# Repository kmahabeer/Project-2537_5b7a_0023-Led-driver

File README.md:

# LED Driver Circuit

Welcome to my photogrammetry project! Within this repository, you will find the KiCad PCB design, as well as the firmware for the LED driver circuit. The LED driver circuit is a crucial component in my photogrammetry project.

## Introduction

My photogrammetry project focuses on creating photorealistic digital clones using a low-budget image capture system with precise illumination facilitated by several LED driver circuits. Precise, multispectral lighting is important for accurate image capture. The images captured are used to recreate texture maps, including diffuse, specular, and roughness maps. Additionally, the images captured serve as valuable training data for creating deepfake models.

The LED driver circuit consists of constant current drivers powering five LEDs, including RGB LEDs, a PC Amber LED, and a neutral white LED. Each circuit incorporates a cost-effective 8-bit Microchip PIC16 microcontroller. Ethernet communication between a main computer through a Power over Ethernet (PoE) switch will be used<sup><a href="#item1">[1]</a></sup>. The microcontroller will most likely implement a lightweight TCP/IP stack where a main computer sends either UDP or TCP packets. While a UDP or TCP packet can be sent via simple commands from the main computer, a custom application will be developed to automate this process once several LED driver circuits are implemented.

Please note that the resources herein are intended solely for this specific project and should not be used elsewhere. My intent for creating the photogrammetry project is my own personal use, and is not intended to create digital clones of anyone besides myself.

## Components

Some important components included in the schematic:

- Microchip PIC16F18026
- Microchip PD70210
- Cree LED JE2835 3V N-Class LEDs
- Luxeon 2835E Neutral White LEDs

## Directory Structure

- `LED-driver-kicad/`: KiCad schematic files (.sch), KiCad PCB layout files (.kicad_pcb) for the main circuit.
- `firmware/`: Any firmware-related code for the microcontroller.
- `Documentation/`: Any relevant documentation or datasheets used in the design.

## References

<ol>
<li id="item1">
“IEEE Standard for Information technology-- Local and metropolitan area networks-- Specific requirements-- Part 3: CSMA/CD Access Method and Physical Layer Specifications Amendment 3: Data Terminal Equipment (DTE) Power via the Media Dependent Interface (MDI) Enhancements” <i>IEEE Standards Association</i>, 30 Oct. 2009, <a href="https://standards.ieee.org/ieee/802.3at/4553/" target="_blank" rel="noopener noreferrer">standards.ieee.org/ieee/802.3at/4553/</a>.
</li>
</ol>

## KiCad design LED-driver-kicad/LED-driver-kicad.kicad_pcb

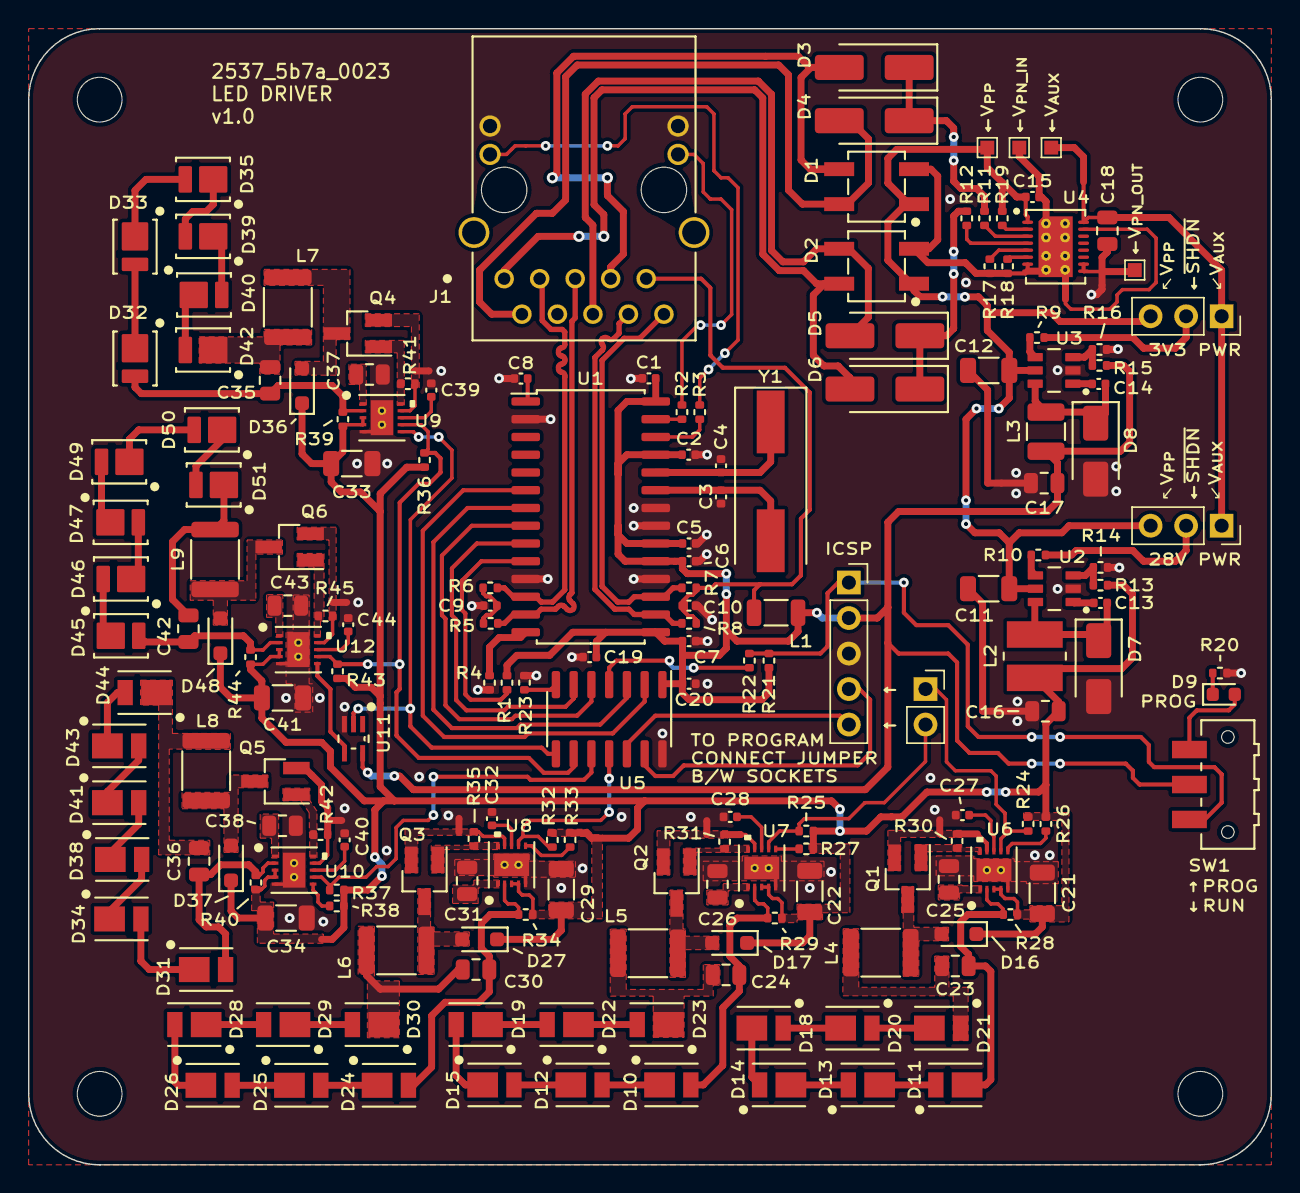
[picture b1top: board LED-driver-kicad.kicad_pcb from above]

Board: 2 copper layers, 88.9 x 81.3 mm, 192 parts (0 on the bottom side), 140 nets.

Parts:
C1, C2, C5, C6, C7, C9, C10, C13, C14, C15, C20: 100n; C_0402_1005Metric
C3, C4: 18p; C_0402_1005Metric
C8: 10u; C_0402_1005Metric
C11, C12: 2u2; C_1206_3216Metric
C16, C18, C23, C24, C25, C26, C30, C31, C35, C36, C37, C38, C42, C43: 4u7; C_0805_2012Metric
C17: 22u; C_0805_2012Metric
C19: 10n; C_0402_1005Metric
C21, C22, C29, C33, C34, C41: 10u; C_1206_3216Metric
C27, C28, C32, C39, C40, C44: 470p; C_0402_1005Metric
D1, D2: D_Bridge_+A-A; D_TO-269AA_4-BESOP_Diodes_MB10S-13
D3, D4, D5, D6: D; D_SMA_Handsoldering
D7, D8: SMC SS110; D_SMA
D9: GREEN; LED_0603_1608Metric
D10, D12, D15, D19, D22, D23: GREEN; LED_Cree-JE2835_3V_NClass_Group-1
D11, D13, D14, D18, D20, D21: RED; LED_Cree-JE2835_3V_NClass_Group-2
D16, D17, D27, D36, D37, D48: SD103AWS; D_SOD-323_HandSoldering
D24, D25, D26, D28, D29, D30: BLUE; LED_Cree-JE2835_3V_NClass_Group-1
D31, D34, D38, D41, D43, D44: PCAmber; LED_Cree-JE2835_3V_NClass_Group-1
D32, D33, D35, D39, D40, D42, D45, D46, D47, D49, D50, D51: White; LED_Lumiled_Luxeon_2835E_3V
H1, H2, H3, H4: MountingHole; MountingHole_3.2mm_M3
J1: ARJM11C7-114-BA-EW2; Connector_RJ45_Abracon_ARJM11C7-114-BA-EW2
J2, J3: Conn_01x03_Socket; PinSocket_1x03_P2.54mm_Vertical
J4: Conn_01x05_Socket; PinSocket_1x05_P2.54mm_Vertical
J5: Conn_01x02_Socket; PinSocket_1x02_P2.54mm_Vertical
L1: Ferrite Bead; L_1206_3216Metric
L2: 100u; L_TDK_VLS4015CX-6R8M-H
L3: 22u; L_1210_3225Metric
L4, L5, L6, L7, L8, L9: 330u; L_1812_4532Metric
NT1, NT2, NT3, NT4, NT5, NT6, NT7, NT8, NT9, NT10: NetTie_2; NetTie-2_SMD_Pad0.5mm
Q1, Q2, Q3, Q4, Q5, Q6: Q_NMOS_GDS; SOT-23_Handsoldering
R1, R11, R12, R14, R16, R21, R30, R31, R35, R41, R42, R45: 10k; R_0402_1005Metric
R2, R3: 1k; R_0402_1005Metric
R4: 2k32; R_0402_1005Metric
R5, R6, R7, R8: 49R9; R_0402_1005Metric
R9, R10, R24, R25, R26, R27, R32, R33, R36, R37, R38, R43: 100k; R_0402_1005Metric
R13: 357k; R_0402_1005Metric
R15: 33k; R_0402_1005Metric
R17: 60k4; R_0402_1005Metric
R18: 30R9; R_0402_1005Metric
R19: 25k; R_0402_1005Metric
R20: 100; R_0402_1005Metric
R22, R23: 470; R_0402_1005Metric
R28, R29, R34, R39, R40, R44: 1.43; R_0402_1005Metric
SW1: SW_SPDT; SW_SPDT_CK-JS102011SAQN
TP1, TP2, TP3, TP4: TestPoint; TestPoint_Pad_1.0x1.0mm
U1: ENC28J60x-SO; SOIC-28W_7.5x17.9mm_P1.27mm
U2, U3: LV2862XLVDDCR; SOT-23-Thin-6_DDC0006A-MFG_Regulator_Voltage_TI_LV2862XLVDD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
U4: PD70210A; DFN-16_5X4_MCH-Interface_PoE_Microchip_PD70210A
U5: PIC16F18026-ISL; SOIC-14_3.9x8.7mm_P1.27mm
U6, U7, U8, U9, U10, U12: MIC3205YML-TR; MLF-10_ML_MCH-Driver_LED_Microchip_MIC3205YML-TR
U11: 74AHC1G14; SOT-353-DCK5-Logic_Diodes_74AHC1G14SE-7
Y1: 25MHz; Crystal_SMD_HC49-SD

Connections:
+3.3V: C1.1, C2.1, C5.1, C6.1, C7.1, C17.1, C19.1, C20.1, J4.2, L1.1, L3.2, R1.2, R15.1, R21.1, SW1.2 (B), U1.15 (VDDTX), U1.19 (VDDRX), U1.20 (VDDPLL), U1.25 (VDDOSC), U1.28 (VDD), U5.1 (VDD), U11.5 (VCC)
+28V: C16.1, C21.1, C22.1, C29.1, C33.1, C34.1, C41.1, D16.1 (K), D17.1 (K), D27.1 (K), D36.1 (K), D37.1 (K), D48.1 (K), L2.2, R13.1, R24.1, R25.1, R26.1, R27.1, R28.1, R29.1, R32.1, R33.1, R34.1, R36.1, R37.1, R38.1, R39.1, R40.1, R43.1, R44.1, U6.3 (VIN), U6.4 (VINS), U7.3 (VIN), U7.4 (VINS), U8.3 (VIN), U8.4 (VINS), U9.3 (VIN), U9.4 (VINS), U10.3 (VIN), U10.4 (VINS), U12.3 (VIN), U12.4 (VINS)
/Ethernet/RJ45_LED_L_ANODE: J1.13 (LED), R2.2
/Ethernet/RJ45_LED_R_ANODE: J1.11 (LED), R3.2
/Ethernet/RJ45_RD+: J1.5 (RD+), R5.1, U1.13 (TPIN+)
/Ethernet/RJ45_RD-: J1.3 (RD-), R6.1, U1.12 (TPIN-)
/Ethernet/RJ45_TCT: C10.1, J1.9 (TCT), L1.2, R7.2, R8.1
/Ethernet/RJ45_TD+: J1.10 (TD+), R7.1, U1.17 (TPOUT+)
/Ethernet/RJ45_TD-: J1.8 (TD-), R8.2, U1.16 (TPOUT-)
/LEDs - amber and white/PGND_AMBER: NT8.2, Q5.3 (S), R42.2, U10.9 (PGND)
/LEDs - amber and white/PGND_WHITE: NT9.1, Q4.3 (S), R41.2, U9.9 (PGND)
/LEDs - amber and white/PGND_WHITE_P: NT10.1, Q6.3 (S), R45.2, U12.9 (PGND)
/LEDs/PGND_BLUE: NT7.2, Q3.3 (S), R35.2, U8.9 (PGND)
/LEDs/PGND_GREEN: NT5.2, Q2.3 (S), R31.2, U7.9 (PGND)
/LEDs/PGND_RED: NT6.2, Q1.3 (S), R30.2, U6.9 (PGND)
/Microcontroller/MCU_ICSP_MCLR: J4.1, R21.2, R22.1, SW1.1 (A)
/Power/3V3_C_{IN}_GND: C12.2, NT2.1
/Power/3V3_~SHDN: J2.2, R9.2
/Power/28V_C_{IN}_GND: C11.2, NT1.1
/Power/28V_~SHDN: J3.2, R10.2
/Power/VAUX: C18.1, J2.1, J3.1, TP3.1, U4.16 (VAUX)
/Power/VPN_IN: C15.2, D1.3 (-), D2.3 (-), NT3.1, R17.2, R18.2, TP2.1, U4.7 (VPN_IN), U4.8 (VPN_IN), U4.17 (ePAD)
/Power/VPN_OUT: C18.2, NT4.2, TP4.1, U4.9 (VPN_OUT), U4.10 (VPN_OUT)
/Power/VPP: C11.1, C12.1, C15.1, D1.1 (+), D2.1 (+), J2.3, J3.3, R19.1, TP1.1, U2.5 (VIN), U3.5 (VIN), U4.1 (VPP)
/Power/WA_EN: NT3.2, U4.15 (WA_EN)
GND: C1.2, C2.2, C3.1, C4.1, C5.2, C6.2, C7.2, C8.2, C9.2, C10.2, C16.2, C17.2, C19.2, C20.2, C21.2, C22.2, C25.2, C26.2, C27.2, C28.2, C29.2, C31.2, C32.2, C33.2, C34.2, C37.2, C38.2, C39.2, C40.2, C41.2, C43.2, C44.2, D7.2 (A), D8.2 (A), J1.12 (LED), J1.14 (LED), J4.3, NT1.2, NT2.2, NT4.1, NT5.1, NT6.1, NT7.1, NT8.1, NT9.2, NT10.2, R4.1, R14.2, R16.2, R20.1, R23.1, U1.2 (VSS), U1.11 (VSSRX), U1.18 (VSSTX), U1.21 (VSSPLL), U1.22 (VSSOSC), U2.2 (GND), U3.2 (GND), U5.14 (VSS), U6.5 (AGND), U6.11 (ePAD), U7.5 (AGND), U7.11 (ePAD), U8.5 (AGND), U8.11 (ePAD), U9.5 (AGND), U9.11 (ePAD), U10.5 (AGND), U10.11 (ePAD), U11.3 (GND), U12.5 (AGND), U12.11 (ePAD)
MCU_CCP1: R36.2, R43.2, U5.9 (RC1), U9.7 (DIM), U12.7 (DIM)
MCU_CCP2: R37.2, U5.10 (RC0), U10.7 (DIM)
MCU_PWM3_OUT: R32.2, U5.11 (RA2), U8.7 (DIM)
MCU_PWM4_OUT: J5.2, R25.2, U7.7 (DIM)
MCU_PWM5_OUT: J5.1, R24.2, U6.7 (DIM)
MCU_SPI_ETH_CS: U1.9 (~CS), U5.6 (RC4)
MCU_SPI_SCK: U1.8 (SCK), U5.5 (RC5)
MCU_SPI_SDI/MOSI: U1.6 (SO), U5.2 (RA5)
MCU_SPI_SDO/MISO: U1.7 (SI), U5.3 (RA4)
MCU_WHITE_LED: U5.8 (RC2), U9.6 (EN), U11.2
unnamed: C9.1, R5.2, R6.2
unnamed: D3.1 (K), D4.1 (K), R11.2
unnamed: D5.1 (K), D6.1 (K), R12.1
unnamed: C13.2, D7.1 (K), L2.1, U2.6 (SW)
unnamed: C14.2, D8.1 (K), L3.1, U3.6 (SW)
unnamed: D9.2 (A), SW1.3 (C)
unnamed: D9.1 (K), R20.2
unnamed: C24.1, D10.2 (A), R29.2, U7.2 (CS)
unnamed: D10.1 (K), D12.2 (A)
unnamed: C23.1, D11.2 (A), R28.2, U6.2 (CS)
unnamed: D11.1 (K), D13.2 (A)
unnamed: D12.1 (K), D15.2 (A)
unnamed: D13.1 (K), D14.2 (A)
unnamed: D14.1 (K), D18.2 (A)
unnamed: D15.1 (K), D19.2 (A)
unnamed: D16.2 (A), L4.2, Q1.2 (D)
unnamed: D17.2 (A), L5.2, Q2.2 (D)
unnamed: D18.1 (K), D20.2 (A)
unnamed: D19.1 (K), D22.2 (A)
unnamed: D20.1 (K), D21.2 (A)
unnamed: C23.2, D21.1 (K), L4.1
unnamed: D22.1 (K), D23.2 (A)
unnamed: C24.2, D23.1 (K), L5.1
unnamed: C30.1, D24.2 (A), R34.2, U8.2 (CS)
unnamed: D24.1 (K), D25.2 (A)
unnamed: D25.1 (K), D26.2 (A)
unnamed: D26.1 (K), D28.2 (A)
unnamed: D27.2 (A), L6.2, Q3.2 (D)
unnamed: D28.1 (K), D29.2 (A)
unnamed: D29.1 (K), D30.2 (A)
unnamed: C30.2, D30.1 (K), L6.1
unnamed: C36.1, D31.2 (A), R40.2, U10.2 (CS)
unnamed: D31.1 (K), D34.2 (A)
unnamed: C35.1, D32.2 (A), R39.2, U9.2 (CS)
unnamed: D32.1 (K), D33.2 (A)
unnamed: D33.1 (K), D35.2 (A)
unnamed: D34.1 (K), D38.2 (A)
unnamed: D35.1 (K), D39.2 (A)
unnamed: D36.2 (A), L7.2, Q4.2 (D)
unnamed: D37.2 (A), L8.2, Q5.2 (D)
unnamed: D38.1 (K), D41.2 (A)
unnamed: D39.1 (K), D40.2 (A)
unnamed: D40.1 (K), D42.2 (A)
unnamed: D41.1 (K), D43.2 (A)
unnamed: C35.2, D42.1 (K), L7.1
unnamed: D43.1 (K), D44.2 (A)
unnamed: C36.2, D44.1 (K), L8.1
unnamed: C42.1, D45.2 (A), R44.2, U12.2 (CS)
unnamed: D45.1 (K), D46.2 (A)
unnamed: D46.1 (K), D47.2 (A)
unnamed: D47.1 (K), D49.2 (A)
unnamed: D48.2 (A), L9.2, Q6.2 (D)
unnamed: D49.1 (K), D50.2 (A)
unnamed: D50.1 (K), D51.2 (A)
unnamed: C42.2, D51.1 (K), L9.1
unnamed: J4.4, U5.13 (RA0/ICSPDAT)
unnamed: J4.5, U5.12 (RA1/ICSPCLK)
unnamed: Q1.1 (G), R30.1, U6.10 (DRV)
unnamed: Q2.1 (G), R31.1, U7.10 (DRV)
unnamed: Q3.1 (G), R35.1, U8.10 (DRV)
unnamed: Q4.1 (G), R41.1, U9.10 (DRV)
unnamed: Q5.1 (G), R42.1, U10.10 (DRV)
unnamed: Q6.1 (G), R45.1, U12.10 (DRV)
unnamed: R2.1, U1.27 (LEDA)
unnamed: R3.1, U1.26 (LEDB)
unnamed: C3.2, U1.23 (OSC1), Y1.2
unnamed: C4.2, U1.24 (OSC2), Y1.1
unnamed: R4.2, U1.14 (RBIAS)
unnamed: C8.1, U1.1 (VCAP)
unnamed: R1.1, U1.10 (~RESET)
unnamed: C13.1, U2.1 (CB)
unnamed: R13.2, R14.1, U2.3 (FB)
unnamed: R10.1, U2.4 (~SHDN)
unnamed: C14.1, U3.1 (CB)
unnamed: R15.2, R16.1, U3.3 (FB)
unnamed: R9.1, U3.4 (~SHDN)
unnamed: R18.1, U4.6 (RCLS)
unnamed: R19.2, U4.2 (RDET)
unnamed: R17.1, U4.5 (RREF)
unnamed: R11.1, U4.3 (SUPP_S1)
unnamed: R12.2, U4.4 (SUPP_S2)
unnamed: R23.2, U5.7 (RC3)
unnamed: R22.2, U5.4 (~MCLR/Vpp/RA3)
unnamed: C27.1, U6.8 (CTIMER)
unnamed: R26.2, U6.6 (EN)
unnamed: C25.1, U6.1 (VCC)
unnamed: C28.1, U7.8 (CTIMER)
unnamed: R27.2, U7.6 (EN)
unnamed: C26.1, U7.1 (VCC)
unnamed: C32.1, U8.8 (CTIMER)
unnamed: R33.2, U8.6 (EN)
unnamed: C31.1, U8.1 (VCC)
unnamed: C39.1, U9.8 (CTIMER)
unnamed: C37.1, U9.1 (VCC)
unnamed: C40.1, U10.8 (CTIMER)
unnamed: R38.2, U10.6 (EN)
unnamed: C38.1, U10.1 (VCC)
unnamed: C44.1, U12.8 (CTIMER)
unnamed: U11.4, U12.6 (EN)
unnamed: C43.1, U12.1 (VCC)
RJ45_VC1+: D1.4, D3.2 (A), J1.7 (VC1+)
RJ45_VC1-: D1.2, D4.2 (A), J1.2 (VC1-)
RJ45_VC2+: D2.4, D5.2 (A), J1.6 (VC2+)
RJ45_VC2-: D2.2, D6.2 (A), J1.1 (VC2-)

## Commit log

2023-07-19 docs: create README.md
2023-07-19 create kicad project
2023-07-22 add gitignore
2023-07-22 docs: update README.md
2023-07-22 add symbols and footprints
2023-07-22 update KiCad schematic
2023-07-27 chore: add kicad library as submodule
2023-07-27 chore: add RJ45 connector and PoE controller symbols to kicad project library
2023-07-27 add separate hierarchical sheets for ethernet and main microcontroller
2023-07-27 chore: update kicad library submodule
2023-07-27 chore: update ethernet.kicad_sch
2023-07-27 chore: update Microcontroller.kicad_sch
2023-07-27 update symbol library locations
2023-07-27 update Memory_Microchip_25AA02E64T-IOT import
2023-07-27 update ENC28J60x-SO circuit
2023-07-27 update main schematic sheet and microcontroller
2023-07-27 remove unused libraries
2023-07-30 update library submodule and imports
2023-07-30 update schematic for RJ45 connector and Ethernet controller
2023-07-30 update schematic for main microcontroller
2023-07-30 add schematics for power controller and LEDs
2023-07-30 update main schematic sheet
2023-08-01 update Power schematic
2023-08-01 remove surge protection and wall adapter circuit
2023-08-01 update RGB LED driver circuits
2023-08-02 update *MCLR switch for microcontroller
2023-08-02 remove EEPROM MAC address IC
2023-08-02 remove VDDA decoupling
2023-08-02 add schematic sheet for white and PC amber LED
2023-08-02 update RGB LEDs
2023-08-02 connect unused IO to pull down resistor
2023-08-02 replace MOSFETs with generic n-channel MSOFETs
2023-08-02 replace push-pull MOSFET circuit with LED driver with inverter gate enable
2023-08-02 update comments and title blocks
2023-08-02 update 3V3 power supply circuit
2023-08-02 update 28V power supply circuit
2023-08-02 update component designators
2023-08-03 resolve Electrical Rules Checker (ERC) errors and warnings
2023-08-03 update footprints
2023-08-03 update footprint assignments
2023-08-04 update library submodule
2023-08-05 initial PCB layout
2023-08-08 update initial components layout
2023-08-12 add test points, net ties to schematics
2023-08-12 update PCB traces and planes
2023-08-14 update silkscreen layer for component designators
2023-08-14 update PCB version number
